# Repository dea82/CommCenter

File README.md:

# CommCenter
Communication center between Ethernet, RS485 and RF.

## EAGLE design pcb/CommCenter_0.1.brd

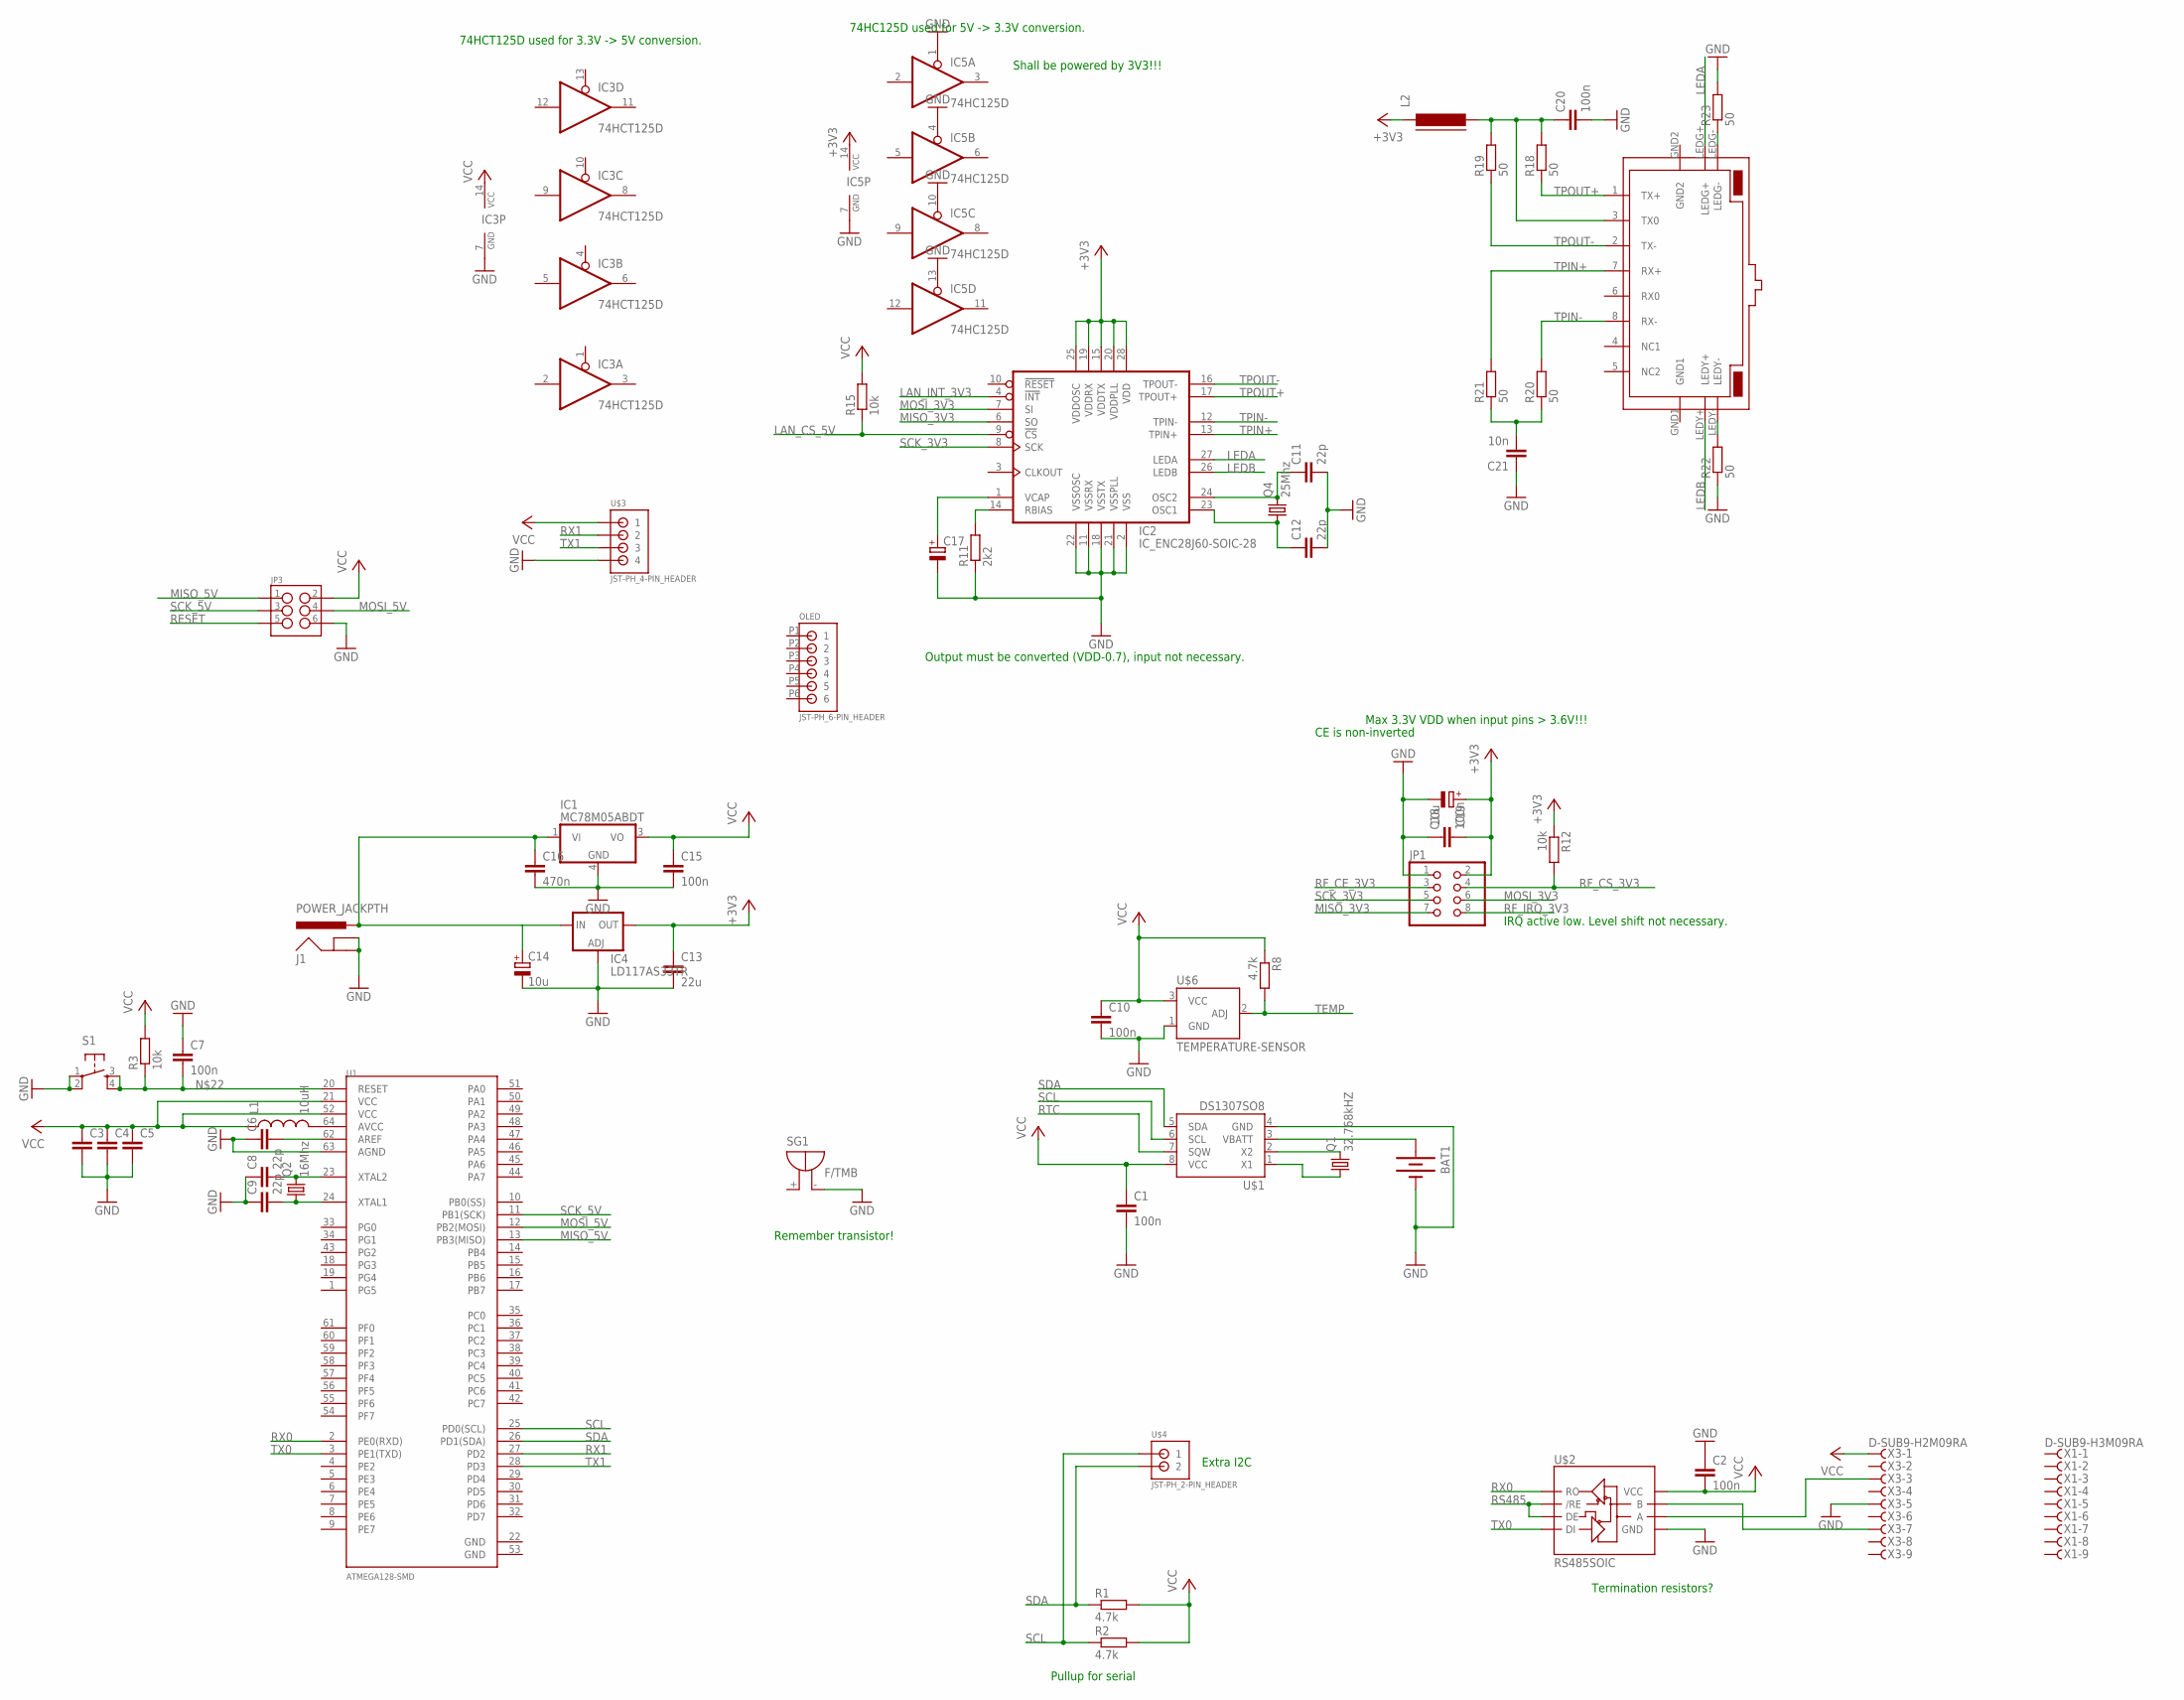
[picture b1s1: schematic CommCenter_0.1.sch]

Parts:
BAT1: BATTERY12PTH; BATTCON_12MM_PTH
C1, C2, C7, C10, C15, C18, C20: 100n; C0805
C3, C4, C5, C6: C-EUC0805; C0805
C8, C9, C11, C12: 22p; C0805
C13: 22u; C1206
C14, C19: 10u; 153CLV-0405
C16: 470n; C0805
C17: CPOL-EU153CLV-0405; 153CLV-0405
C21: 10n; C0805
IC1: MC78M05ABDT; DPACK_3
IC2: IC_ENC28J60-SOIC-28; SOIC-28W
IC3: 74HCT125D; SO14
IC4: LD117AS33TR; SOT223
IC5: 74HC125D; SO14
J1: POWER_JACKPTH; POWER_JACK_PTH
JP1: PINHD-2X4; 2X04
JP3: M03X2SHROUD; 2X3-SHROUDED
L1: 10uH; 0805
L2: FERRITE-PTH-10; L10
OLED: JST-PH_6-PIN_HEADER; JST_B6B-PH_HEADER
Q1: 32.768kHZ; TC26H
Q2: 16Mhz; HC49/S
Q4: 25Mhz; HC49/S
R1, R2, R8: 4.7k; R0805
R3, R12, R15: 10k; R0805
R11: 2k2; R0805
R18, R19, R20, R21, R22, R23: 50; R0805
S1: TAC_SWITCHSMD; TACTILE-SWITCH-SMD
SG1: F/TMB
U1: ATMEGA128-SMD; TQFP64_14X14MM
U$1: DS1307SO8; SO08
U$2: RS485SOIC; SO08
U$3: JST-PH_4-PIN_HEADER; JST_B4B-PH_HEADER
U$4: JST-PH_2-PIN_HEADER; JST_B2B-PH_HEADER
U$5: RJ45-TRAFO-L
U$6: TEMPERATURE-SENSOR; TO-92
X1: D-SUB9-H3M09RA; H3M09RA
X3: D-SUB9-H2M09RA; H2M09RA

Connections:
+3V3: C13.1, C18.2, C19.+, IC2.15 (VDDTX), IC2.19 (VDDRX), IC2.20 (VDDPLL), IC2.25 (VDDOSC), IC2.28 (VDD), IC4.4 (OUT), IC5.14 (VCC), JP1.2, L2.1, R12.1
GND: BAT1.GND (-), C1.2, C2.1, C3.2, C4.2, C5.2, C6.1, C7.1, C8.1, C9.1, C10.2, C11.2, C12.2, C13.2, C14.-, C15.2, C16.2, C17.-, C18.1, C19.-, C20.2, C21.1, IC1.4 (GND), IC2.2 (VSS), IC2.11 (VSSRX), IC2.18 (VSSTX), IC2.21 (VSSPLL), IC2.22 (VSSOSC), IC3.7 (GND), IC4.1 (ADJ), IC5.1 (OE), IC5.4 (OE), IC5.7 (GND), IC5.10 (OE), IC5.13 (OE), J1.GND, J1.GNDBREAK, JP1.1, JP3.6, R11.1, R22.1, R23.2, S1.1, S1.2, SG1.-, U1.63 (AGND), U$1.4 (GND), U$2.5 (GND), U$3.P4 (4), U$6.1 (GND), X3.5
GND1: U$5.GND1
GND2: U$5.GND2
LAN_CS_5V: R15.1
LAN_INT_3V3: IC2.4 (!INT)
LEDA: IC2.27 (LEDA), U$5.LEDG+
LEDB: IC2.26 (LEDB), U$5.LEDY+
MISO_3V3: IC2.6 (SO), JP1.7
MISO_5V: JP3.1, U1.13 (PB3(MISO))
MOSI_3V3: IC2.7 (SI), JP1.6
MOSI_5V: JP3.4, U1.12 (PB2(MOSI))
unnamed: C8.2, Q2.2, U1.23 (XTAL2)
unnamed: L1.2, U1.64 (AVCC)
unnamed: Q1.1, U$1.1 (X1)
unnamed: Q1.2, U$1.2 (X2)
unnamed: BAT1.VCC@1 (+), U$1.3 (VBATT)
unnamed: U$2.6 (A), X3.3
unnamed: C9.2, Q2.1, U1.24 (XTAL1)
unnamed: C11.1, IC2.24 (OSC2), Q4.2
unnamed: C6.2, U1.62 (AREF)
unnamed: C14.+, C16.1, IC1.1 (VI), IC4.3 (IN), J1.PWR
unnamed: U$2.7 (B), X3.7
unnamed: C12.1, IC2.23 (OSC1), Q4.1
unnamed: IC2.14 (RBIAS), R11.2
unnamed: C17.+, IC2.1 (VCAP)
unnamed: C20.1, L2.2, R18.2, R19.2, U$5.3 (TX0)
unnamed: C7.2, R3.1, S1.3, S1.4, U1.20 (RESET)
unnamed: C21.2, R20.1, R21.1
unnamed: R22.2, U$5.LEDY-
unnamed: R23.1, U$5.LEDG-
RESET: JP3.5
RF_CE_3V3: JP1.3
RF_CS_3V3: JP1.4, R12.2
RF_IRQ_3V3: JP1.8
RS485: U$2.2 (/RE), U$2.3 (DE)
RTC: U$1.7 (SQW)
RX0: U1.2 (PE0(RXD)), U$2.1 (RO)
RX1: U1.27 (PD2), U$3.P2 (2)
SCK_3V3: IC2.8 (SCK), JP1.5
SCK_5V: JP3.3, U1.11 (PB1(SCK))
SCL: R2.1, U1.25 (PD0(SCL)), U$1.6 (SCL), U$4.P1 (1)
SDA: R1.1, U1.26 (PD1(SDA)), U$1.5 (SDA), U$4.P2 (2)
TEMP: R8.2, U$6.2 (ADJ)
TPIN+: IC2.13 (TPIN+), R21.2, U$5.7 (RX+)
TPIN-: IC2.12 (TPIN-), R20.2, U$5.8 (RX-)
TPOUT+: IC2.17 (TPOUT+), R18.1, U$5.1 (TX+)
TPOUT-: IC2.16 (TPOUT-), R19.1, U$5.2 (TX-)
TX0: U1.3 (PE1(TXD)), U$2.4 (DI)
TX1: U1.28 (PD3), U$3.P3 (3)
VCC: C1.1, C2.2, C3.1, C4.1, C5.1, C10.1, C15.1, IC1.3 (VO), IC3.14 (VCC), JP3.2, L1.1, R1.2, R2.2, R3.2, R8.1, R15.2, U1.21 (VCC), U1.52 (VCC), U$1.8 (VCC), U$2.8 (VCC), U$3.P1 (1), U$6.3 (VCC), X3.1

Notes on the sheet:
Pullup for serial
Extra I2C
Max 3.3V VDD when input pins > 3.6V!!!
IRQ active low. Level shift not necessary.
CE is non-inverted
Termination resistors?
74HCT125D used for 3.3V -> 5V conversion.
74HC125D used for 5V -> 3.3V conversion.
Output must be converted (VDD-0.7), input not necessary.
Remember transistor!
Shall be powered by 3V3!!!

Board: 2 copper layers, 60 parts (3 on the bottom side), 43 nets, no tracks yet.

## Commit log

2016-01-28 no message

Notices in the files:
parts and their libraries:
SparkFun-FreqCtrl: Licensing: CC v3.0 Share-Alike You are welcome to use this library for commercial purposes.
SparkFun-DigitalIC: Licensing: Creative Commons ShareAlike 4.0 International - https://creativecommons.org/licenses/by-sa/4.0
